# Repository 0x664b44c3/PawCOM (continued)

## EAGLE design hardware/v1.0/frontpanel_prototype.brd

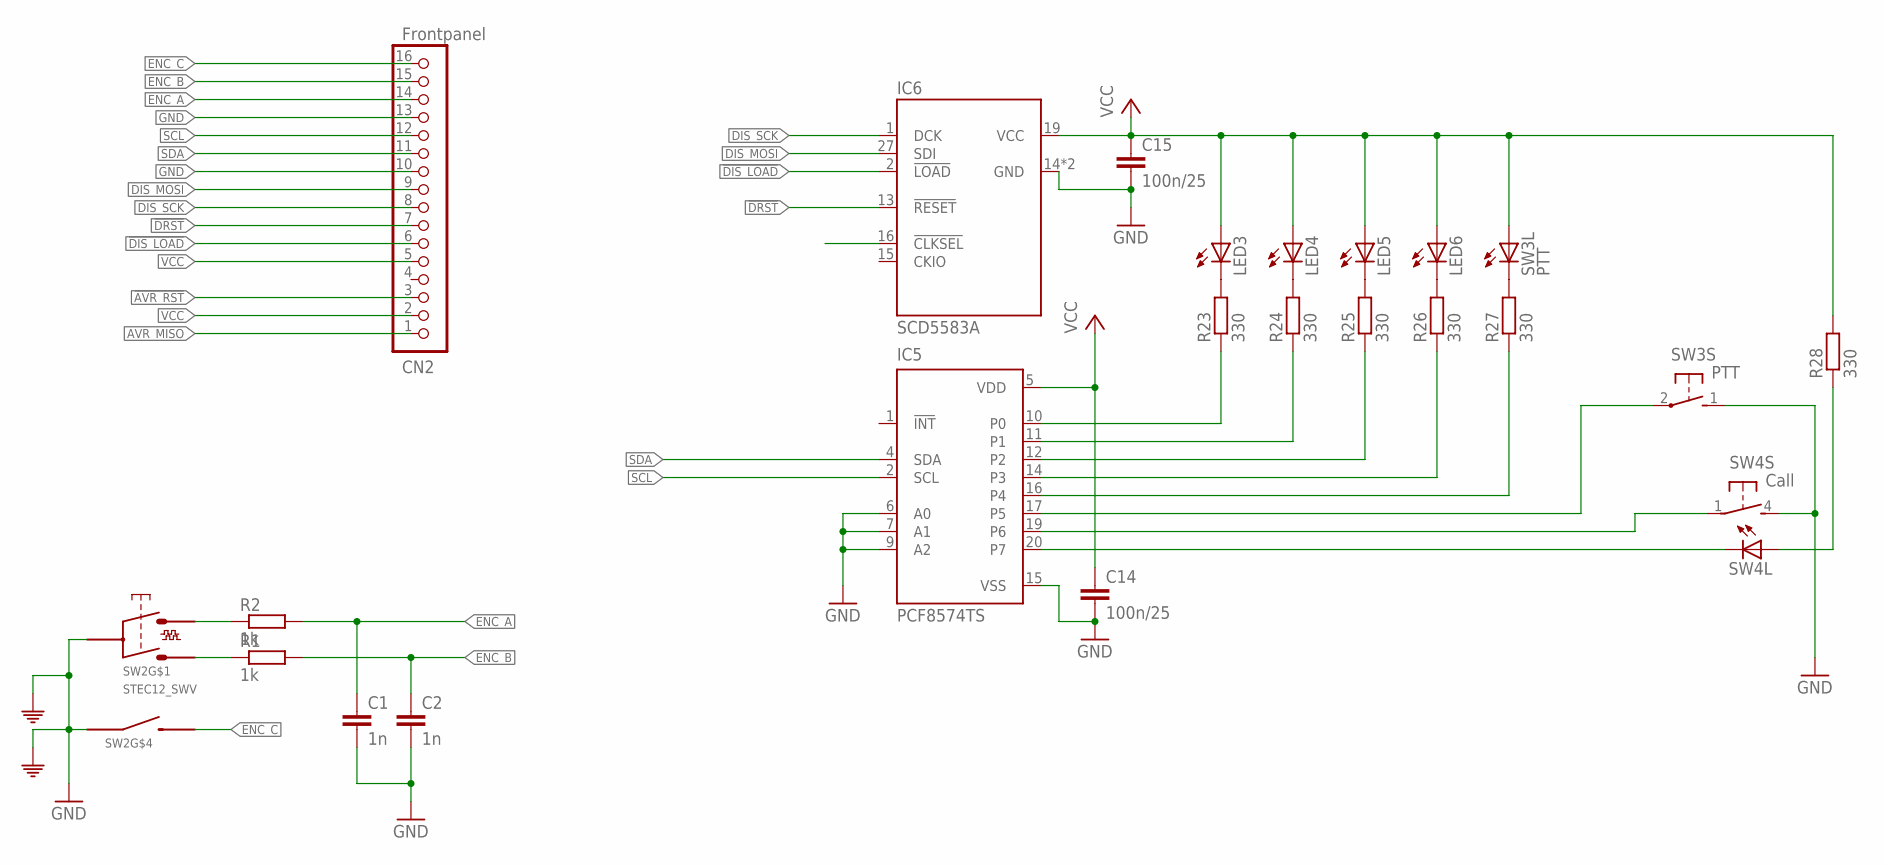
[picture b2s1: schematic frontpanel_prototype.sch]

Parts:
C1, C2: 1n; C0603
C14, C15: 100n/25; C0603
CN2: Frontpanel; MOLEX-505278-1633
IC5: PCF8574TS; SSOP20
IC6: SCD5583A; SCD558XA
LED3, LED4, LED5, LED6: LEDLZR181; LZR181
R1, R2: 1k; R0603
R23, R24, R25, R26, R27, R28: 330; R0603
SW2: STEC12_SWV; STEC12_VERT
SW3: PTT; 6425
SW4: Call; MEC_5G_LED

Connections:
!AVR_RST!: CN2.3
!DIS_LOAD!: CN2.6, IC6.2 (!LOAD!)
!DRST!: CN2.7, IC6.13 (!RESET!)
AVR_MISO: CN2.1
DIS_MOSI: CN2.9, IC6.27 (SDI)
DIS_SCK: CN2.8, IC6.1 (DCK)
ENC_A: C1.1, CN2.14, R2.2
ENC_B: C2.1, CN2.15, R1.2
ENC_C: CN2.16, SW2.Y
GND: C1.2, C2.2, C14.2, C15.2, CN2.10, CN2.13, IC5.6 (A0), IC5.7 (A1), IC5.9 (A2), IC5.15 (VSS), IC6.14 (GND), IC6.28 (GND), SW2.B, SW2.G1, SW2.G2, SW2.X, SW3.1 (S), SW4.4 (S)
unnamed: R2.1, SW2.A
unnamed: R1.1, SW2.C
unnamed: R27.2, SW3.K (C)
unnamed: LED3.K (C), R23.2
unnamed: R28.1, SW4.3 (A)
unnamed: IC5.19 (P6), SW4.1
unnamed: IC5.20 (P7), SW4.2 (C)
unnamed: IC5.17 (P5), SW3.2
unnamed: LED4.K (C), R24.2
unnamed: LED5.K (C), R25.2
unnamed: LED6.K (C), R26.2
unnamed: IC5.16 (P4), R27.1
unnamed: IC5.10 (P0), R23.1
unnamed: IC5.11 (P1), R24.1
unnamed: IC5.12 (P2), R25.1
unnamed: IC5.14 (P3), R26.1
SCL: CN2.12, IC5.2 (SCL)
SDA: CN2.11, IC5.4 (SDA)
VCC: C14.1, C15.1, CN2.2, CN2.5, IC5.5 (VDD), IC6.19 (VCC), LED3.A, LED4.A, LED5.A, LED6.A, R28.2, SW3.A

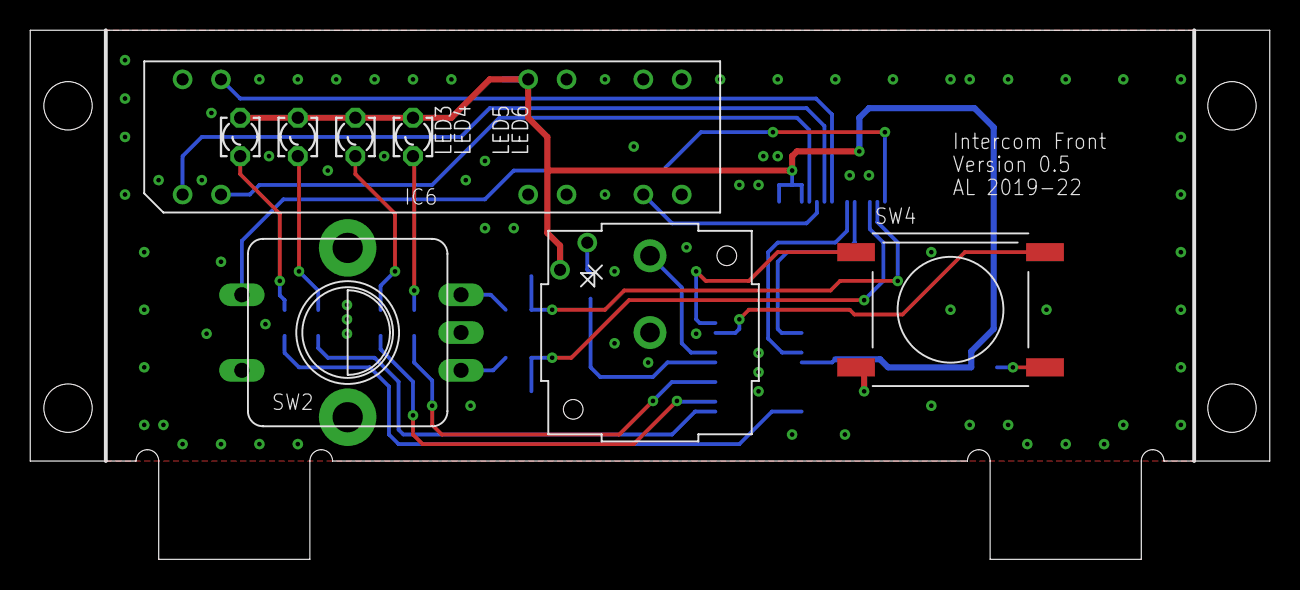
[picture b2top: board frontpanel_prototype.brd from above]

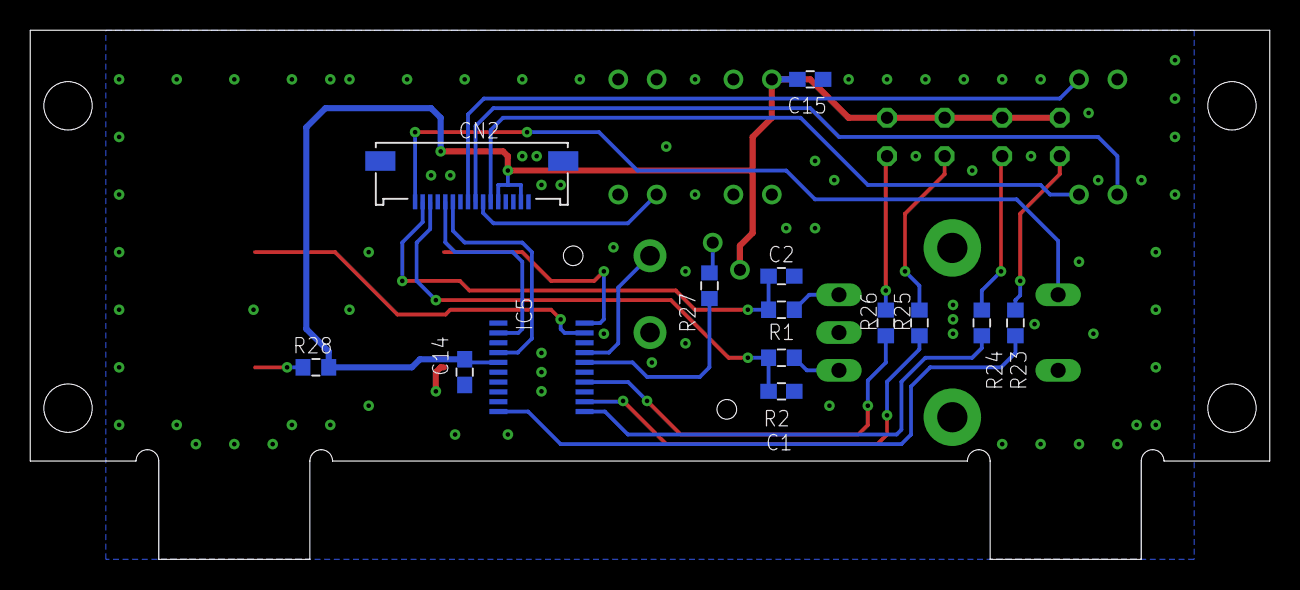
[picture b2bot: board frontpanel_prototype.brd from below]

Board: 2 copper layers, 82.0 x 35.0 mm, 22 parts (14 on the bottom side), 27 nets.

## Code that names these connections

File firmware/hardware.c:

#include <stdint.h>
#include <avr/io.h>
#include <avr/interrupt.h>
#include "hardware.h"
#include "i2c.h"

//system state vars
volatile uint8_t mute_line=1;
volatile uint8_t beep_18=1;
volatile uint8_t call_in=0;
volatile uint8_t call_send=0;
volatile uint8_t call_led=0;
volatile uint8_t mic_mute=0;


const uint8_t sine_tab[] = {0x80, 0x8c, 0x98, 0xa4, 0xb0, 0xbb, 0xc6, 0xd0,
                            0xd9, 0xe2, 0xe9, 0xf0, 0xf5, 0xf9, 0xfc, 0xfe,
                            0xfe, 0xfe, 0xfc, 0xf9, 0xf5, 0xf0, 0xe9, 0xe2,
                            0xd9, 0xd0, 0xc6, 0xbb, 0xb0, 0xa4, 0x98, 0x8c,
                            0x80, 0x73, 0x67, 0x5b, 0x4f, 0x44, 0x39, 0x2f,
                            0x26, 0x1d, 0x16, 0x10, 0x0a, 0x06, 0x03, 0x01,
                            0x01, 0x01, 0x03, 0x06, 0x0a, 0x0f, 0x16, 0x1d,
                            0x26, 0x2f, 0x39, 0x44, 0x4f, 0x5b, 0x67, 0x73};

inline uint8_t sineLookup(uint8_t in) {
	uint8_t v1=0, v2=0;
	uint8_t step = in>>2;
	uint8_t sub=in&3;
	v1 = sine_tab[step++];
	if ((step<sizeof(sine_tab))&&(sub)) {
		uint16_t accu=0;
		v2 = sine_tab[step];
		for (register uint8_t i=0;i<4;++i) {
			if (i<sub)
				accu+=v2;
			else
				accu+=v1;
		}
		accu>>=2;
		v1=accu;
	}
	return v1;
}

struct configBlock sysCfg;

int8_t enc_ctr=0;
volatile uint8_t enc_btn=0;
void update_gpio(void)
{
	if (mute_line)
		PORTB&=~_BV(2);
	else
		PORTB|=_BV(2);

	if (beep_18)
		PORTB|=_BV(1);
	else
		PORTB&=~_BV(1);

	call_in = (PINB & _BV(0))==0;
	enc_btn = (PINC&_BV(5))?0:1;

	if (sysCfg.mic_gain_and_pwr & 0x80)
		PORTC&= ~_BV(3);
	else
		PORTC |= _BV(3);

	if (mic_mute)
		PORTD|= _BV(2);
	else
		PORTD&=~_BV(2);

	switch(sysCfg.mic_gain_and_pwr & cfgMicGainMask)
	{
		case 0:
			PORTD|= _BV(4); // -10 (*)
			PORTD&=~_BV(3); // +20 ( ) -10
			break;
		case 1:
			PORTD&=~_BV(4); // -10 ( )
			PORTD&=~_BV(3); // +20 ( ) 0
			break;
		case 2:
			PORTD|= _BV(4); // -10 (*)
			PORTD|= _BV(3); // +20 (*) +10
			break;
		case 3:
		default:
			PORTD&=~_BV(4); // -10 ( )
			PORTD|= _BV(3); // +20 (*) +20
			break;
	}
	if (call_send)
		PORTA|=_BV(0);
	else
		PORTA&=~_BV(0);
}

void init_beep(void)
{
	//PWM stage 0A on
	TCCR0A = _BV(WGM00) | _BV(WGM01) | _BV(COM0A1);
	TCCR0B = 1;
	OCR0A = 0x80;
}

volatile uint8_t tone_accu=0, tone_vol=0x7f;
volatile uint8_t tone_inc = 0;
volatile uint8_t cycle;
static inline void do_audio(void)
{
	if (tone_inc)
	{
		int16_t tone = sineLookup(tone_accu);
		tone -=128;
		tone *=tone_vol;
		tone/=256;
		tone+=128;

		OCR0A=tone;//(tone_accu&128)?0x80 + tone_vol: 0x80-tone_vol;
		tone_accu+=tone_inc;
	}
	else
	{
		OCR0A=0x80;
	}
}

uint8_t oldPins=0;

ISR(TIMER2_OVF_vect) // 16kHz
{	do_audio();
	uint8_t pins = PINC&0xc0;
	if (oldPins!=pins)
	{
		if (pins == 0x00)
		{
			if (oldPins == 0x80)
				enc_ctr--;
			if (oldPins == 0x40)
				enc_ctr++;
		}
	}
	oldPins = pins;
}

void init_timers(void)
{
	timer_init();
	TCCR2A =  _BV(WGM20) | _BV(WGM21);
	TCCR2B =  _BV(WGM22) | 2;
	OCR2A = 249/2;
	TIMSK2 = _BV(OCIE2A) | _BV(TOIE2);
}

struct tone_task toneQueue[8];
uint8_t tones_queued=0;

void push_tone(uint8_t replace, uint16_t freq, uint16_t duration, uint8_t volume)
{
	if (replace)
		tones_queued=0;
	if (tones_queued == 8)
		tones_queued=7;
	toneQueue[tones_queued].freq = freq;
	toneQueue[tones_queued].duration = duration;
	toneQueue[tones_queued].volume = volume;
	++tones_queued;
}


const uint8_t volumes[6] = {127,  // 0dB
                            90,  // -3dB
                            64,  // -6dB
                            45,  // -9dB
                            32,  // -12dB
                            23   // -15dB
                           };

void beep_setvol(uint8_t volume)
{
	uint8_t tmp = volume;
	if (volume)
	{
		if (tmp>12)
			tmp=12;
		tmp--;
		tone_vol = volumes[5 - (tmp%6)];
		beep_18 = (tmp>5)?0:1;
		update_gpio();
	}
	else
	{
		tone_vol = 0;
	}
}

void update_volume(void)
{
	static uint8_t buffer[2];
	buffer[0] = 0x00 | ((31 - sysCfg.volume) & 0x1f);
	buffer[1] = 0x40 | ((31 - sysCfg.volume) & 0x1f);
	_twi_send_data(0x52, buffer, 2);
	__twi_wait_ready();
}

void update_sidetone( void )
{
	static uint8_t buffer[2];
	buffer[0] = 0x00;
	buffer[1] = sysCfg.sidetone * 0x11;
	_twi_send_data(0x50, buffer, 2);
}

void init_hw(void)
{
	DDRA = 0x09;
	DDRB = 0xde;
	PORTC = 0xe8;
	DDRC = 0x08;
	PORTD = 0x04;
	DDRD = 0x3e;
	SPCR0 = _BV(SPE0)|_BV(MSTR0)|_BV(SPR00)|_BV(DORD0);
}

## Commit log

2019-07-09 initial check in
2019-07-10 ptt handling incl hold done
2021-12-29 "production" version, has been tested in the field
2021-12-29 moved firmware to subdirectory
2021-12-29 added hardware
2021-12-30 added PDF schematics
2021-12-30 added notes on known issues in hw 1.0
2022-01-01 circuit description
